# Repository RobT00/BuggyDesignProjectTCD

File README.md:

# Z8_Machine
Code and hardware for the buggy built by Group Z8 for the 2E10 module at TCD

A demonstration can be seen [here](https://youtu.be/nmqNwGIwm2o).

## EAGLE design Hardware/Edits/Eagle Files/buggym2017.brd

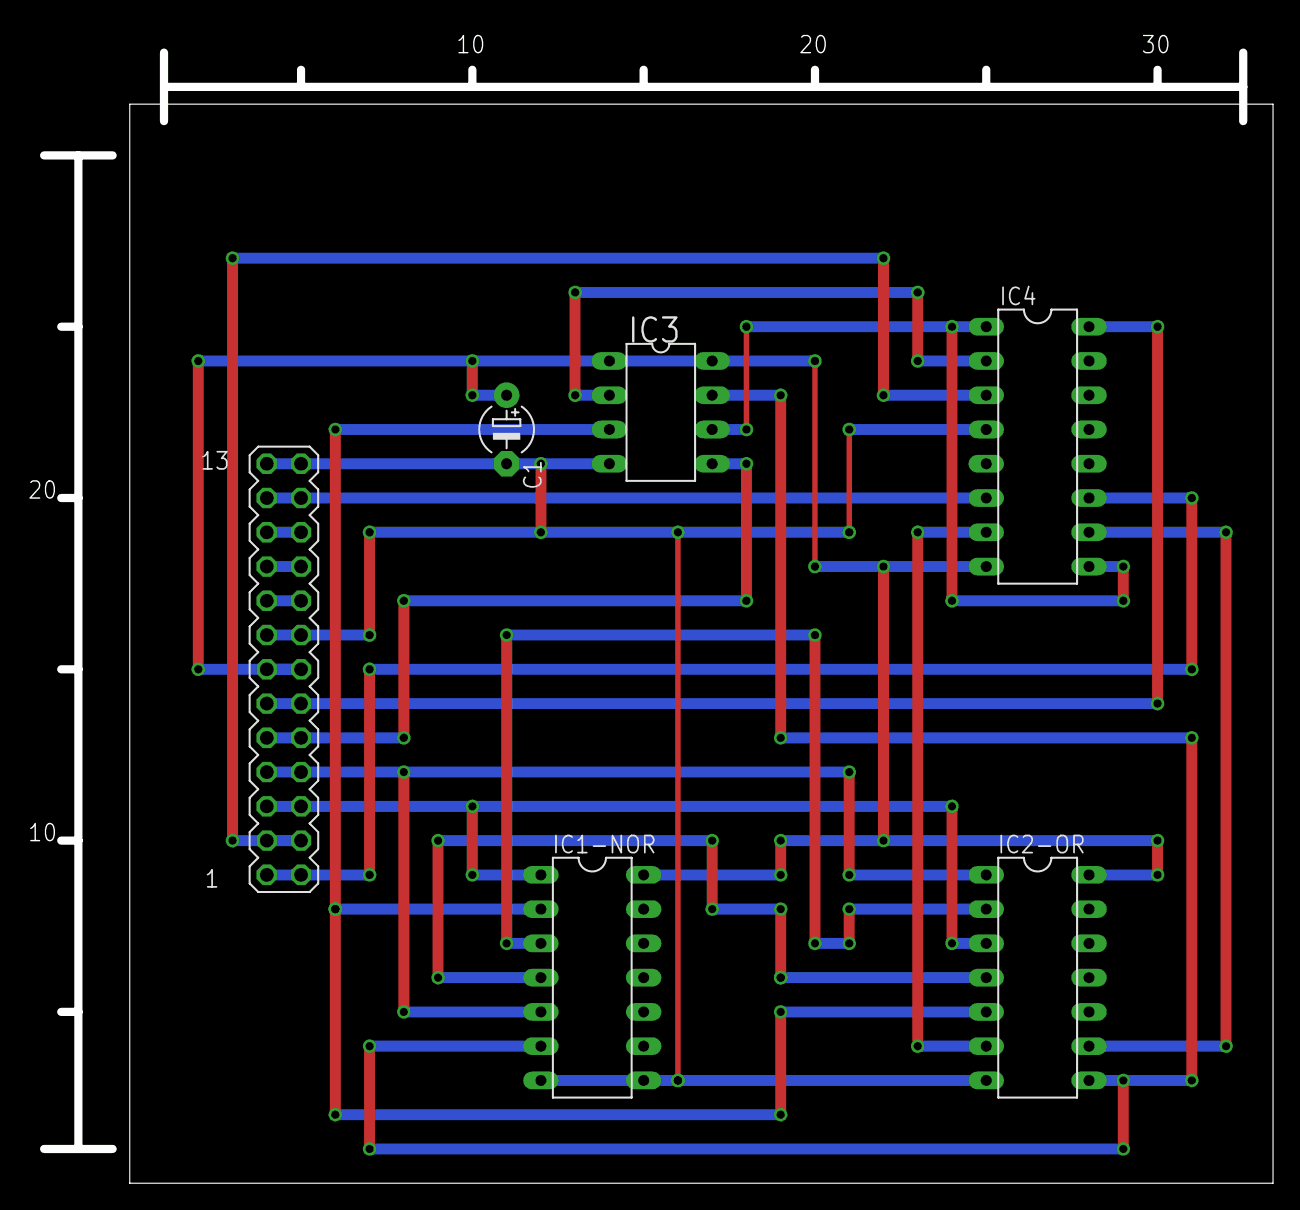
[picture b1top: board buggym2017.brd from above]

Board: 2 copper layers, 91.1 x 83.8 mm, 6 parts (0 on the bottom side), 17 nets.

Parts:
BUGGY_CON: 2E10HDR; 2E10BOARD
C1: E5-4
IC1-NOR: 4001N; DIL14
IC2-OR: 4075N; DIL14
IC3: BCC; DIL8
IC4: L293E; DIL16

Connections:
5V: BUGGY_CON.7, C1.+, IC1-NOR.14, IC2-OR.14, IC3.1, IC3.8, IC4.8
7.2V: BUGGY_CON.6', IC4.16
BCC_COM_LINE: BUGGY_CON.5, IC3.5
GND: BUGGY_CON.8, BUGGY_CON.13', C1.-, IC1-NOR.7, IC2-OR.7, IC3.4, IC4.4
LINK_1: IC1-NOR.3, IC2-OR.2
LINK_2: IC1-NOR.4, IC2-OR.4
LM: IC2-OR.9, IC4.10
LO: IC1-NOR.6, IC2-OR.8, IC3.7
L_EYE: BUGGY_CON.4, BUGGY_CON.4', IC1-NOR.5, IC2-OR.1
unnamed: IC3.2, IC4.2
unnamed: BUGGY_CON.1, IC4.11
unnamed: BUGGY_CON.12, IC4.6
unnamed: BUGGY_CON.2, IC4.3
unnamed: IC3.6, IC4.1, IC4.9
RM: IC2-OR.6, IC4.7
RO: IC1-NOR.2, IC2-OR.5, IC3.3
R_EYE: BUGGY_CON.3, BUGGY_CON.3', IC1-NOR.1, IC2-OR.3

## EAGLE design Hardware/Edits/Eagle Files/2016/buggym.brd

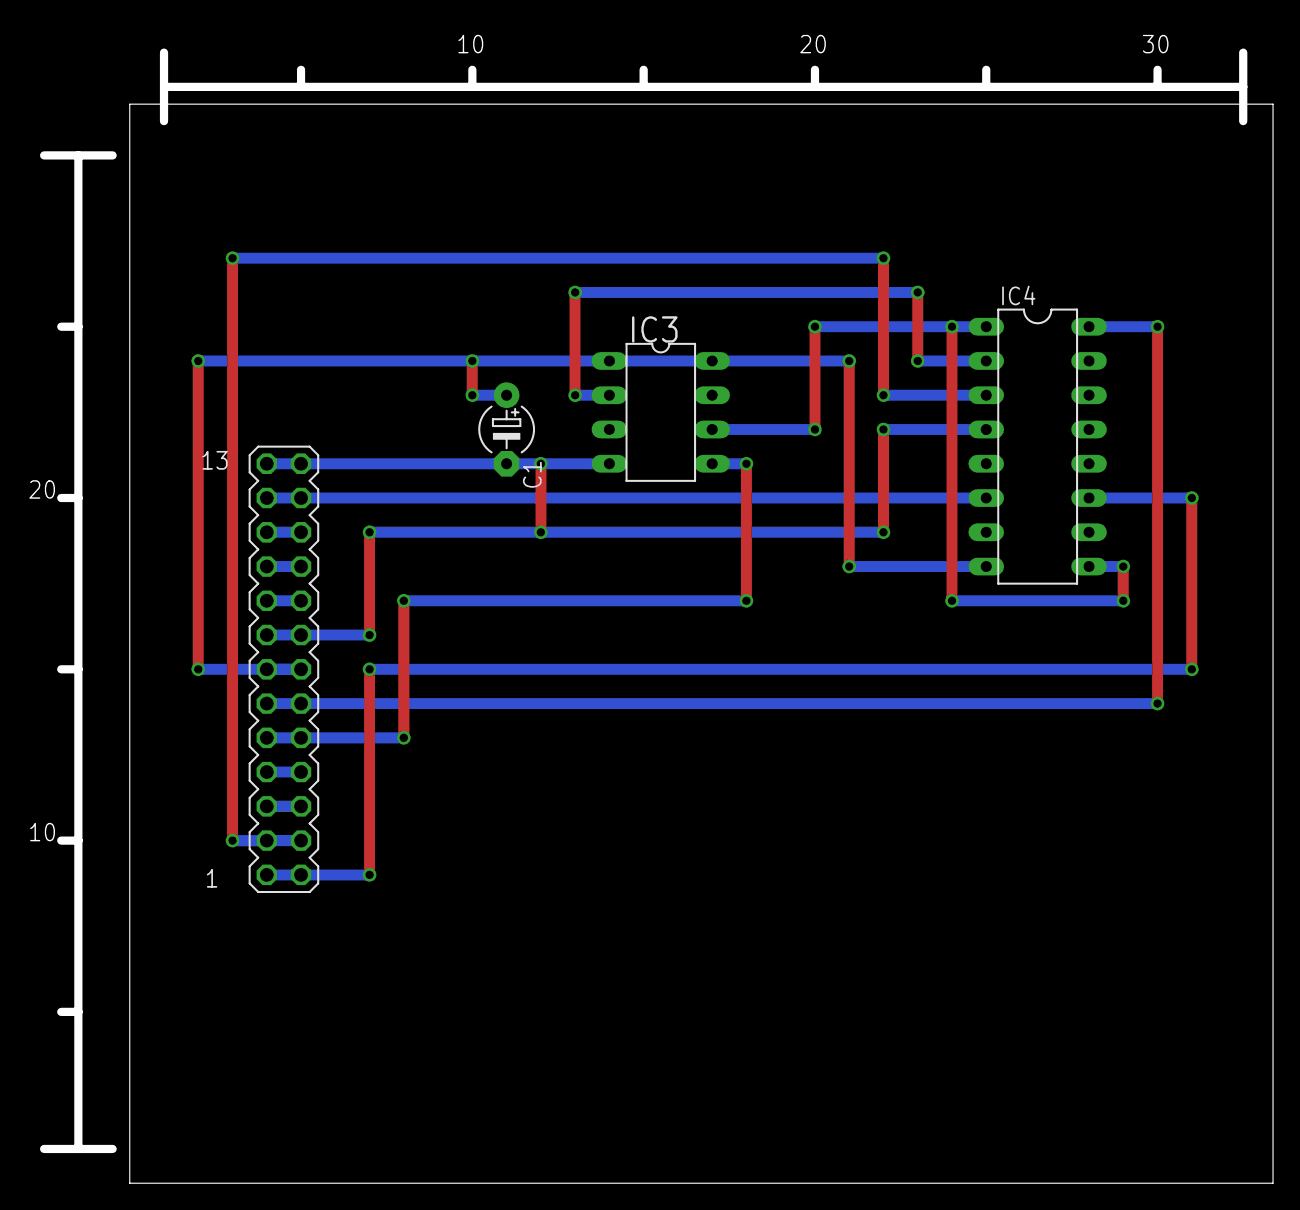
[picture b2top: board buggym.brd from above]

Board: 2 copper layers, 91.1 x 83.8 mm, 4 parts (0 on the bottom side), 9 nets.

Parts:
C1: E5-4
IC3: BCC; DIL8
IC4: L293E; DIL16
U$1: 2E10HDR; 2E10BOARD

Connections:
5V: C1.+, IC3.1, IC3.8, IC4.8, U$1.7
7.2V: IC4.16, U$1.6'
BCC_COM_LINE: IC3.5, U$1.5
GND: C1.-, IC3.4, IC4.4, U$1.8, U$1.13'
unnamed: IC3.2, IC4.2
unnamed: IC4.11, U$1.1
unnamed: IC4.6, U$1.12
unnamed: IC4.3, U$1.2
unnamed: IC3.6, IC4.1, IC4.9

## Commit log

2017-01-17 Created Aron's branch
2017-01-17 Created Rob's branch
2017-01-17 Created Eoin's branch
2017-01-17 Created Alexandra's branch
2017-01-17 Finished creating personal branches
2017-01-23 Created C# skeleton
2017-01-23 Fixed C# project setup
2017-01-23 Moved C# gitignore and gitattributes
2017-01-23 Week 2 labs finished
2017-01-25 Created Eagle project
2017-01-25 Week 2 CS lab
2017-01-26 Removed files that should have been ignored
2017-01-26 Work Done in Logic Lab Week 2
    Truth Table and Logic for circuit
2017-01-26 WIP: Logic Design
    Design 2 contains the basic circuit, with correct truth tables
    Design 3 is the WIP, optimising use of gates
2017-01-26 Fix for error in previous commit
2017-01-26 Logic Circuit Design
    Design 4 contains the circuit design, using two 2-input NOR gates and two 3-input OR gates (satisfying the parameter of using 2 ICs)
2017-01-26 Whitespace fixes
2017-01-27 Removed Multisim security copies
2017-01-27 Added Truth Table
    The PNG file is just a picture of the truth table. The PDF also contains the truth table as well as the (simplified) boolean expressions for each motor and a brief explanation of the logic.
2017-01-30 Work done is CS Lab, Week 3
    C# code for the week 3 lab, asynchronous event handling and logging of chat
2017-02-01 File from Lab
2017-02-01 Work Done in Week 3 HardwareLab
    Work done in Multisim and Eagle
2017-02-01 Tidy
    Tidied up filesystem from HW Lab Week 3
2017-02-05 Created Arduino project
2017-02-05 Created simple hashmap for storing commands and handlers
2017-02-05 Created Bronze sequence diagram
2017-02-06 Wrote communication protocol specification
2017-02-06 Protocol document fixes
2017-02-06 Protocol with IDs
2017-02-06 Week 4 CS Lab
    Arduino and C# code schtuffs
2017-02-07 Circuit Schematics
    Finished circut schematics/layout, pending review on Wednesday 8/2
2017-02-07 Added doc folder from Aron
    For easy/convenient access
2017-02-08 Added Misc Files
2017-02-08 Command definition fixes
2017-02-08 bcc motot control class
2017-02-08 Week 4 Hardware
    Circuit Layouts and Schematics - FINAL
2017-02-08 Rename Folder
2017-02-08 Refactored MotorControls into a class
2017-02-09 Issue #4
    C# code to Implement communictions transciever, created "Communications" class
2017-02-10 Refactored projects
2017-02-10 Created initial model
2017-02-11 Buggy Sketch 11/02/2017
2017-02-11 CommTrans.h file 11/02/2017
2017-02-11 CommTrans.cpp file 11/02/2017
2017-02-12 Renamed CommTrans files
2017-02-12 Fixes in CommTrans
2017-02-12 HashMap now uses Strings instead of char*
2017-02-12 Minor fixes
2017-02-12 LED flash and CommTrans default handler
2017-02-12 Added 'INVALID' message in documentation
2017-02-12 Made HashMap testable
2017-02-13 Added GANTRY_INVALID message
2017-02-13 Created initial Buggy class on the Arduino side
2017-02-13 Tiny fixes
2017-02-13 Lab 5
2017-02-13 Work done in CS lab Week 5
    PING/PONG - Success
    Working on detecting Gantries and going to Park Lane
    Prep for Wizard of OZ
2017-02-13 Refactored Lab 5 Arduino
2017-02-15 Fixed Gantry detection issue
2017-02-15 Rerouted ground and the left motor signal Ground went around the header in a column that is not actually present on the board. Fixed Moved 3 pre-placed wires, so that the left motor signal wire does 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
2017-02-15 Tiny refactor
2017-02-15 Work done in Hardware Lab 5
    Finished schematic and new Arduino Sketch, blink without delay
2017-02-16 Work in C# code
    Should hopefully be sufficient for Week 6 Demo and potentially Week 8. Need to find out how overrides (for parking) are being handled.
2017-02-19 Added ChangeLog.txt
2017-02-19 C# update
    Slight error in code in terms of commands, all should be good for Wizard of OZ Demo
2017-02-20 Added week 3 to ChangeLog.txt
2017-02-20 Added parking to Arduino
2017-02-20 Week 6 CS Lab
    Great Success, work needed on message printing
2017-02-20 Software Lab 6
    Wizzard of Oz doing magic
2017-02-20 Minor refactors
2017-02-24 UltraSonics Module
    Includes .cpp, .h, and original .ino file
2017-02-26 Refactored Ultrasonic Arduino code
2017-02-26 Made CommTrans a pointer
2017-02-26 Updated Bronze sequence diagrams
2017-02-26 Updated ChangeLog.txt
2017-02-26 Removed BlinkWithoutDelay1
2017-02-27 Eagle board more accurately reflects the final board. Thin wires represent deviations from the original given schematic with the BCC and the H-bridge.
2017-02-27 Deleted Eagle backup files
2017-02-27 Gitignore for CLion
2017-02-27 Created Gold sequence diagram
2017-02-27 Cleaned up doc folder
2017-02-28 Typo fixes
2017-03-01 Added PDFs and PNGs
    Of logic board and schematic
2017-03-01 Fixes in ultrasonic
2017-03-02 Basics for Gold Challenge
    The skeletal functions for the gold challenge should be in place. Want to tidy up screen printout, show more information on the screen (possibly) add more contingencies, e.g. if buggy runs out of bat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
2017-03-03 More updates
    Almost there!
2017-03-03 Buggy direction now configurable through constructor
2017-03-05 Made small changes to code
    Code should function for one or two buggies now (i.e. only 1 buggy required for bronze)
2017-03-06 Week 8 Demo
2017-03-06 Week 8 - Bronze Complete
2017-03-13 Tweaks
2017-03-13 Week 9
    Code from beginning of week 9, no implementation of repeat sending
2017-03-13 Week 9 Updates
    Should have working failsafe for "GANTRY_INVALID" and if message is not recieved by buggy first time (or at all!)
2017-03-15 Week 9 Work
    Lots of wok done, introduced buggy power off failsafe, issue with locking
2017-03-15 Added Buggy ACK command
2017-03-15 Buggy decides travel direction based on ID instead of commands
2017-03-15 Lint fixes
2017-03-15 Updated command definition table
2017-03-15 Added Arduino sketch to test Xbee transmission time
2017-03-15 Added sendLocks to Station communications
2017-03-15 Station matching commands based on Regexes. Not tested
2017-03-15 Improved addCommand regex. Not tested
2017-03-16 Colour printing! Not tested
2017-03-16 Better offline handling. Not tested
2017-03-16 Created StopTest
2017-03-20 Made the Buggy great again
2017-03-20 Work in Week 10 lab
    Need to add handlers for messages from buggys
2017-03-20 Command handlers should now be executed on a separate thread Hopefully a custom Thread[Queue] with a ConcurrentQueue will not be necessary
2017-03-21 Improved lights
2017-03-22 Swapped light polarities
2017-03-22 Added INVALID regex handler
2017-03-22 Separated readInput into a function
2017-03-22 Working Gold
    Online/offline working, no regex
2017-03-22 Regex Working
    Tis deadly
2017-03-22 Most up to date version
    Need to tweak settings in terms of clearing input and typing field
2017-03-22 Small fixes
2017-03-26 Ironed out issues with messages hanging around
2017-03-26 Slight error fix
    Forgot to take out line of code that made syn() always return true, was used for testing purposes
2017-03-27 Improving clarity, making print methods self-contained
2017-03-27 Clean TimeTest directory
2017-03-27 Attempt at making Station code clearer, more consistent, and well commented
2017-03-27 Video done
2017-03-27 Updated pins and timings
2017-03-27 Commented Arduino
2017-03-29 Little update
    Pretty colours!
2017-03-29 Small adjustments
2017-03-30 Section name fix
2017-03-30 Shortened lines to a 100 character limit
2017-03-30 Fancy light wave
2017-04-05 Code used in Final Demonstration
2017-04-11 Added schematic for the driver circiut for the LEDs
2017-04-11 Updated documentation
2017-04-11 Cleanup for submission
